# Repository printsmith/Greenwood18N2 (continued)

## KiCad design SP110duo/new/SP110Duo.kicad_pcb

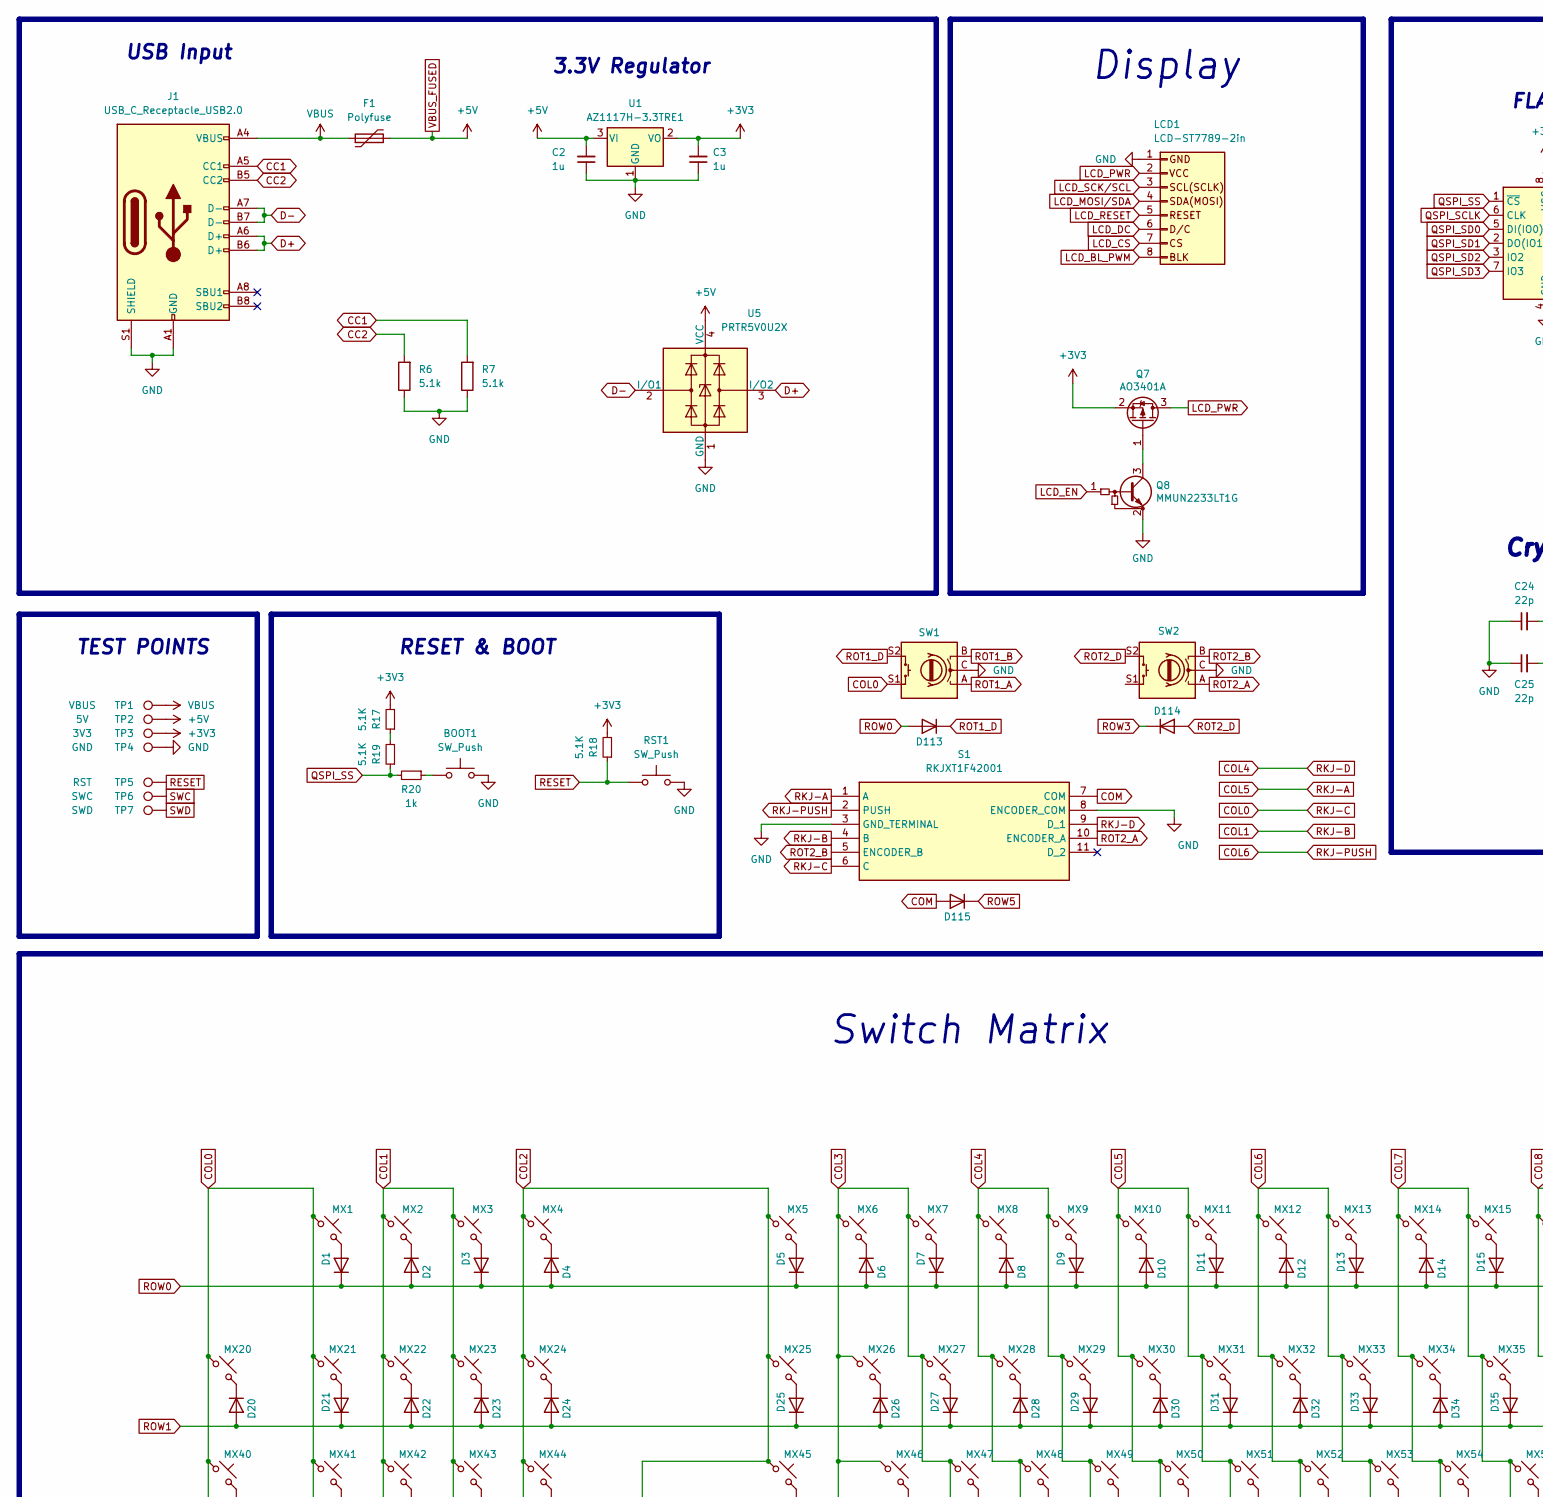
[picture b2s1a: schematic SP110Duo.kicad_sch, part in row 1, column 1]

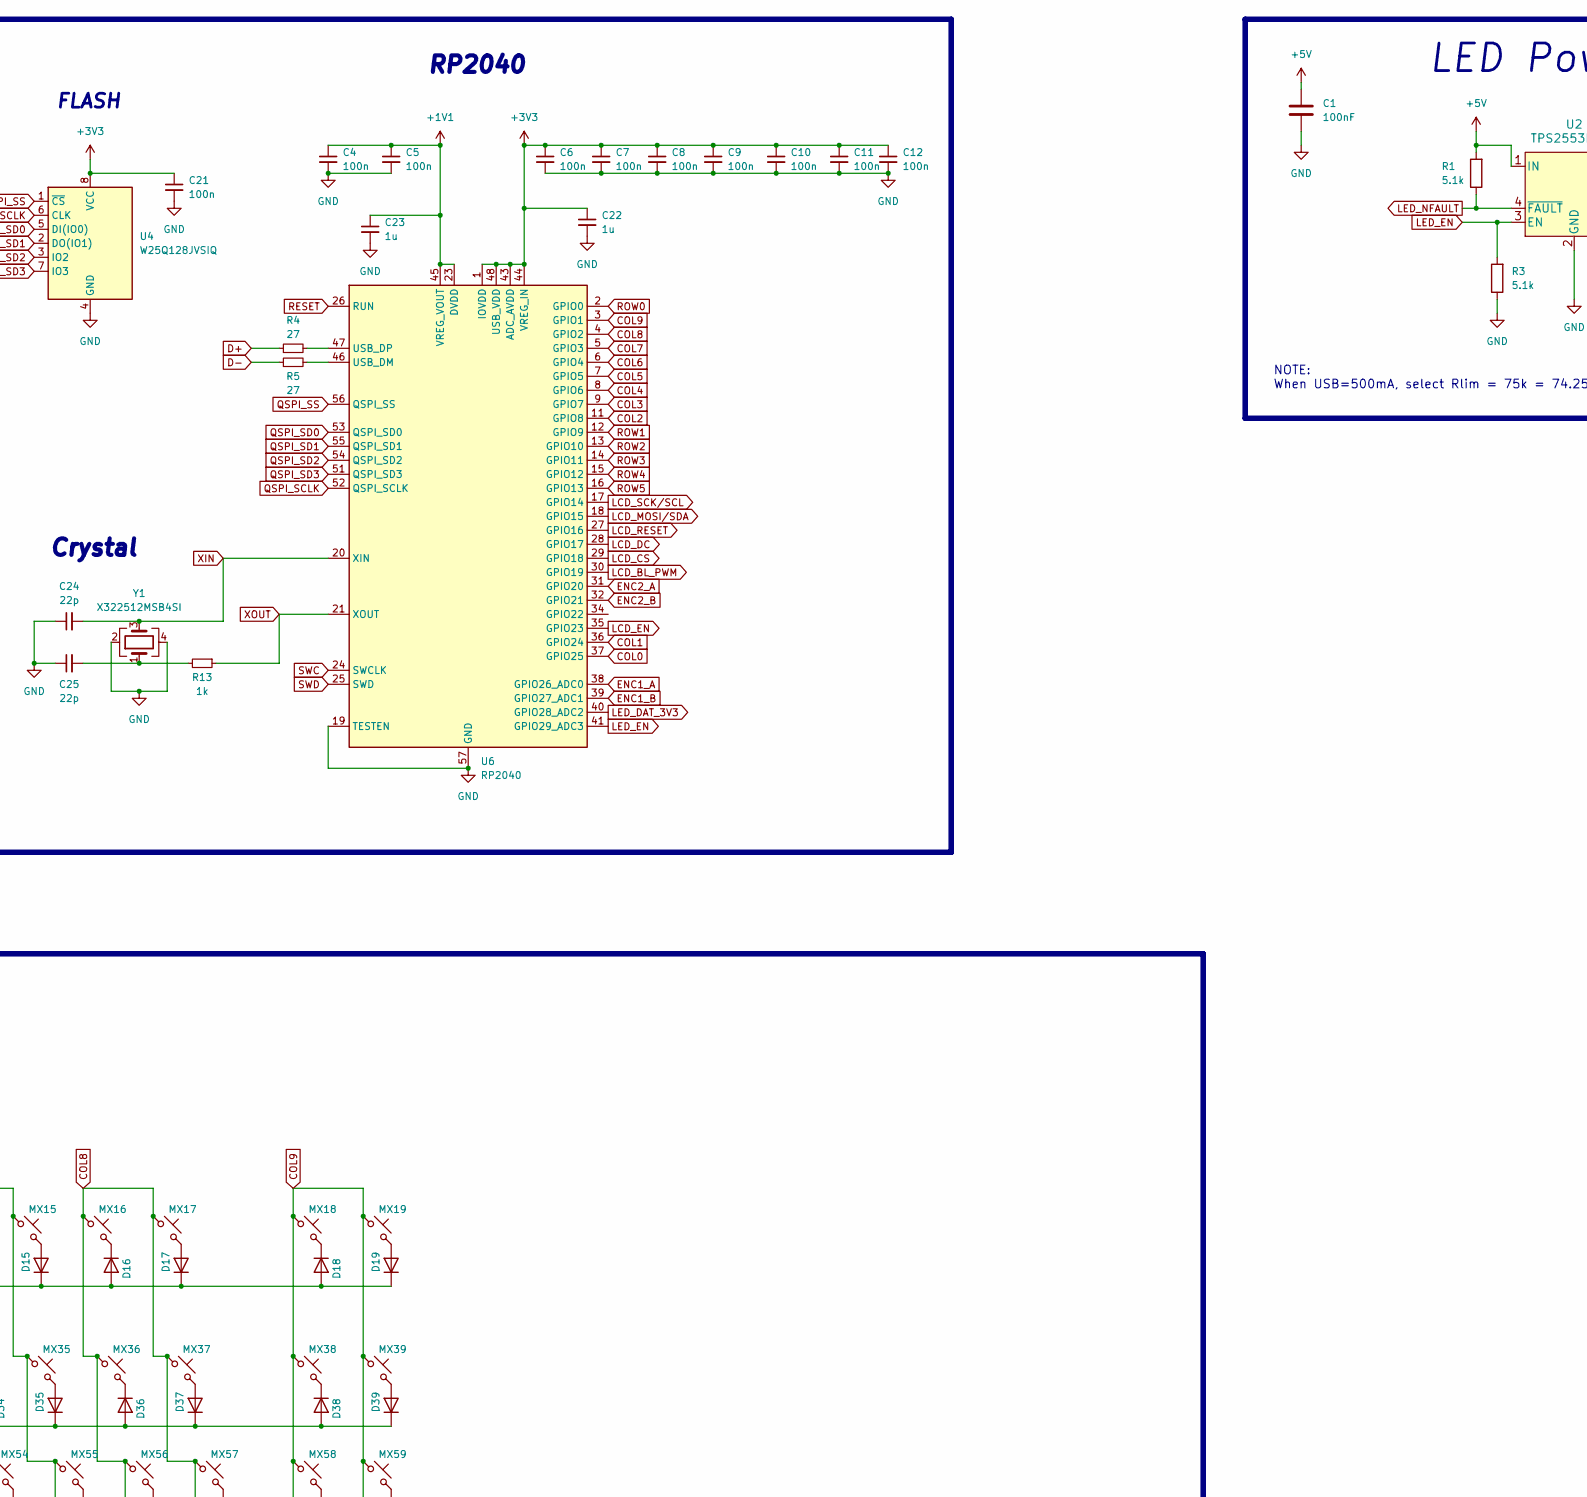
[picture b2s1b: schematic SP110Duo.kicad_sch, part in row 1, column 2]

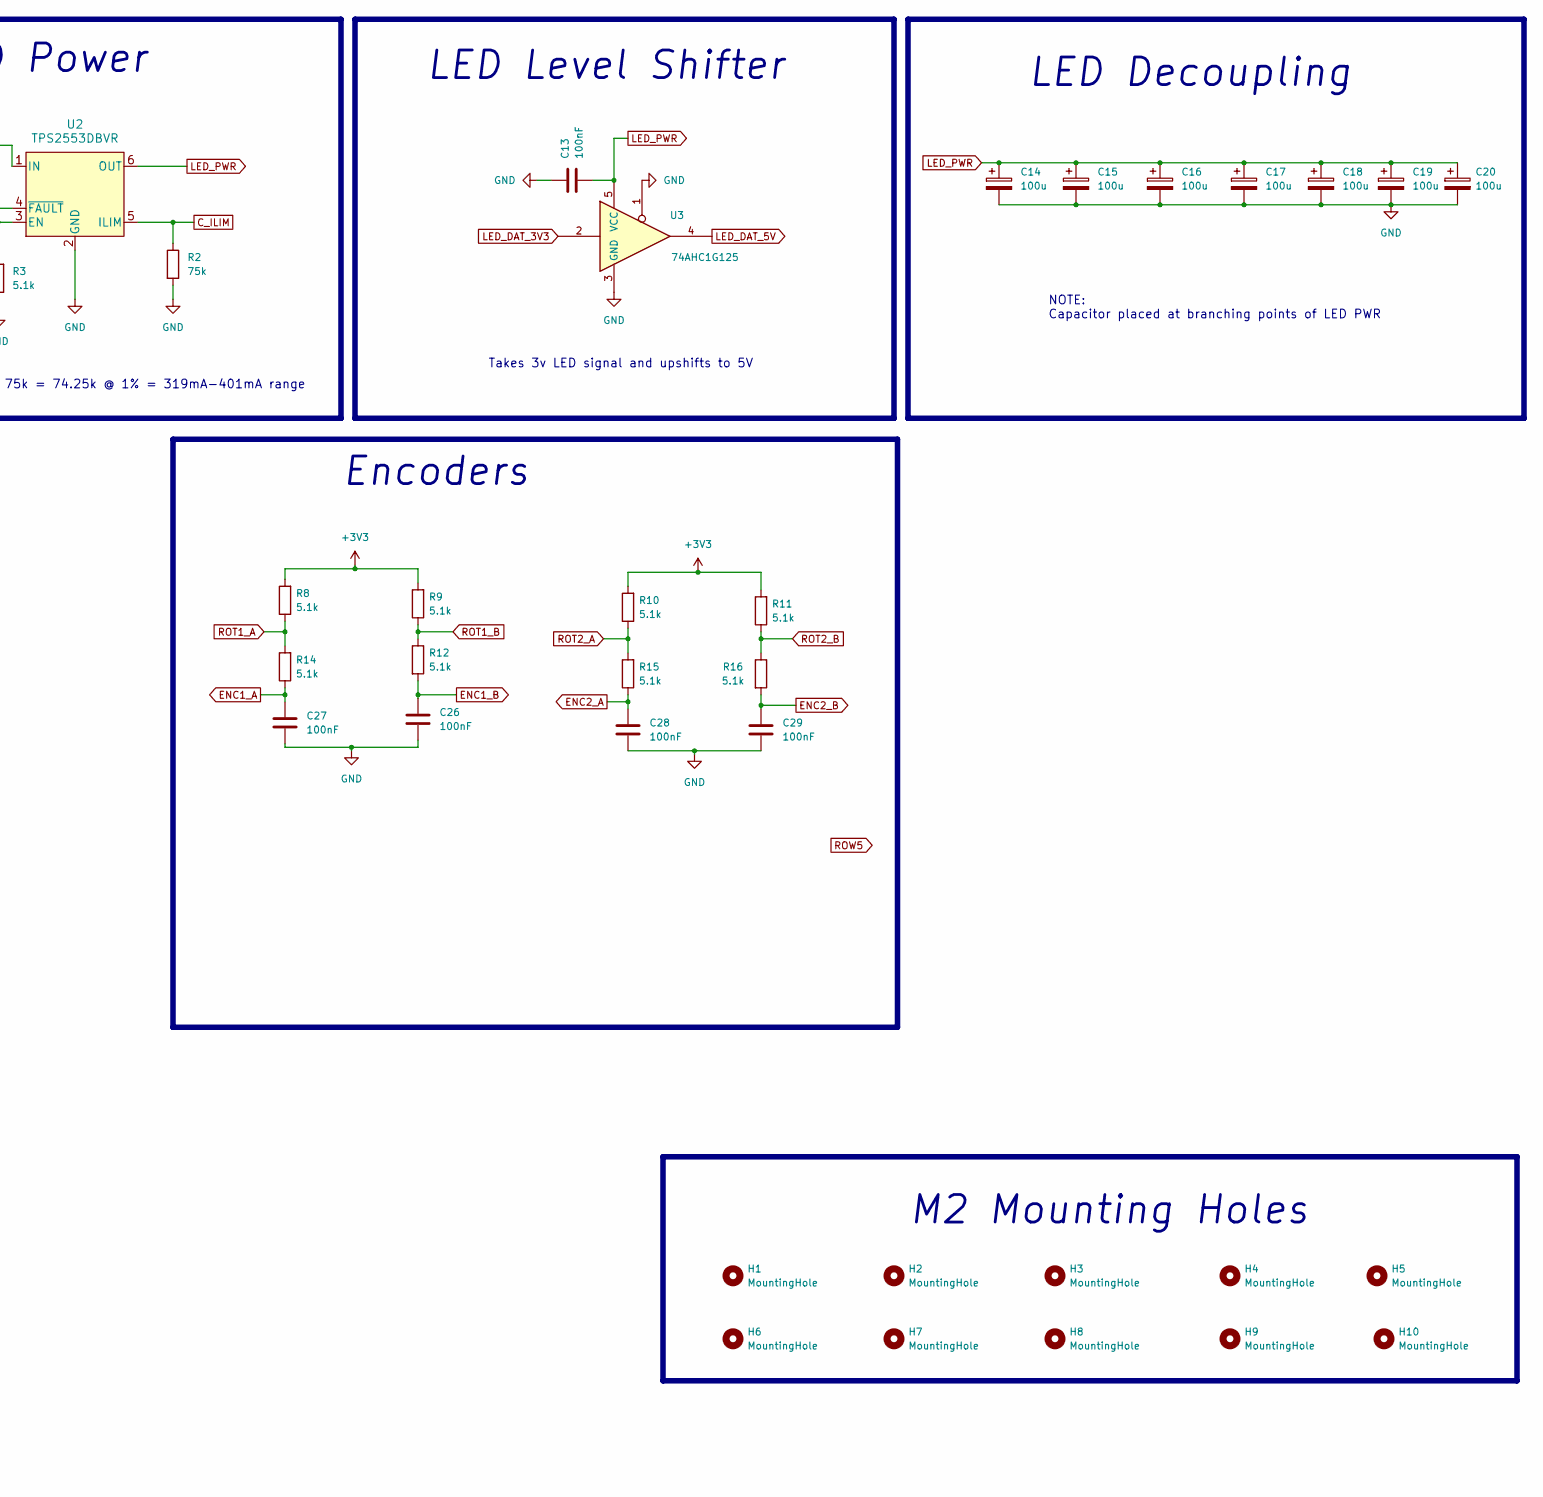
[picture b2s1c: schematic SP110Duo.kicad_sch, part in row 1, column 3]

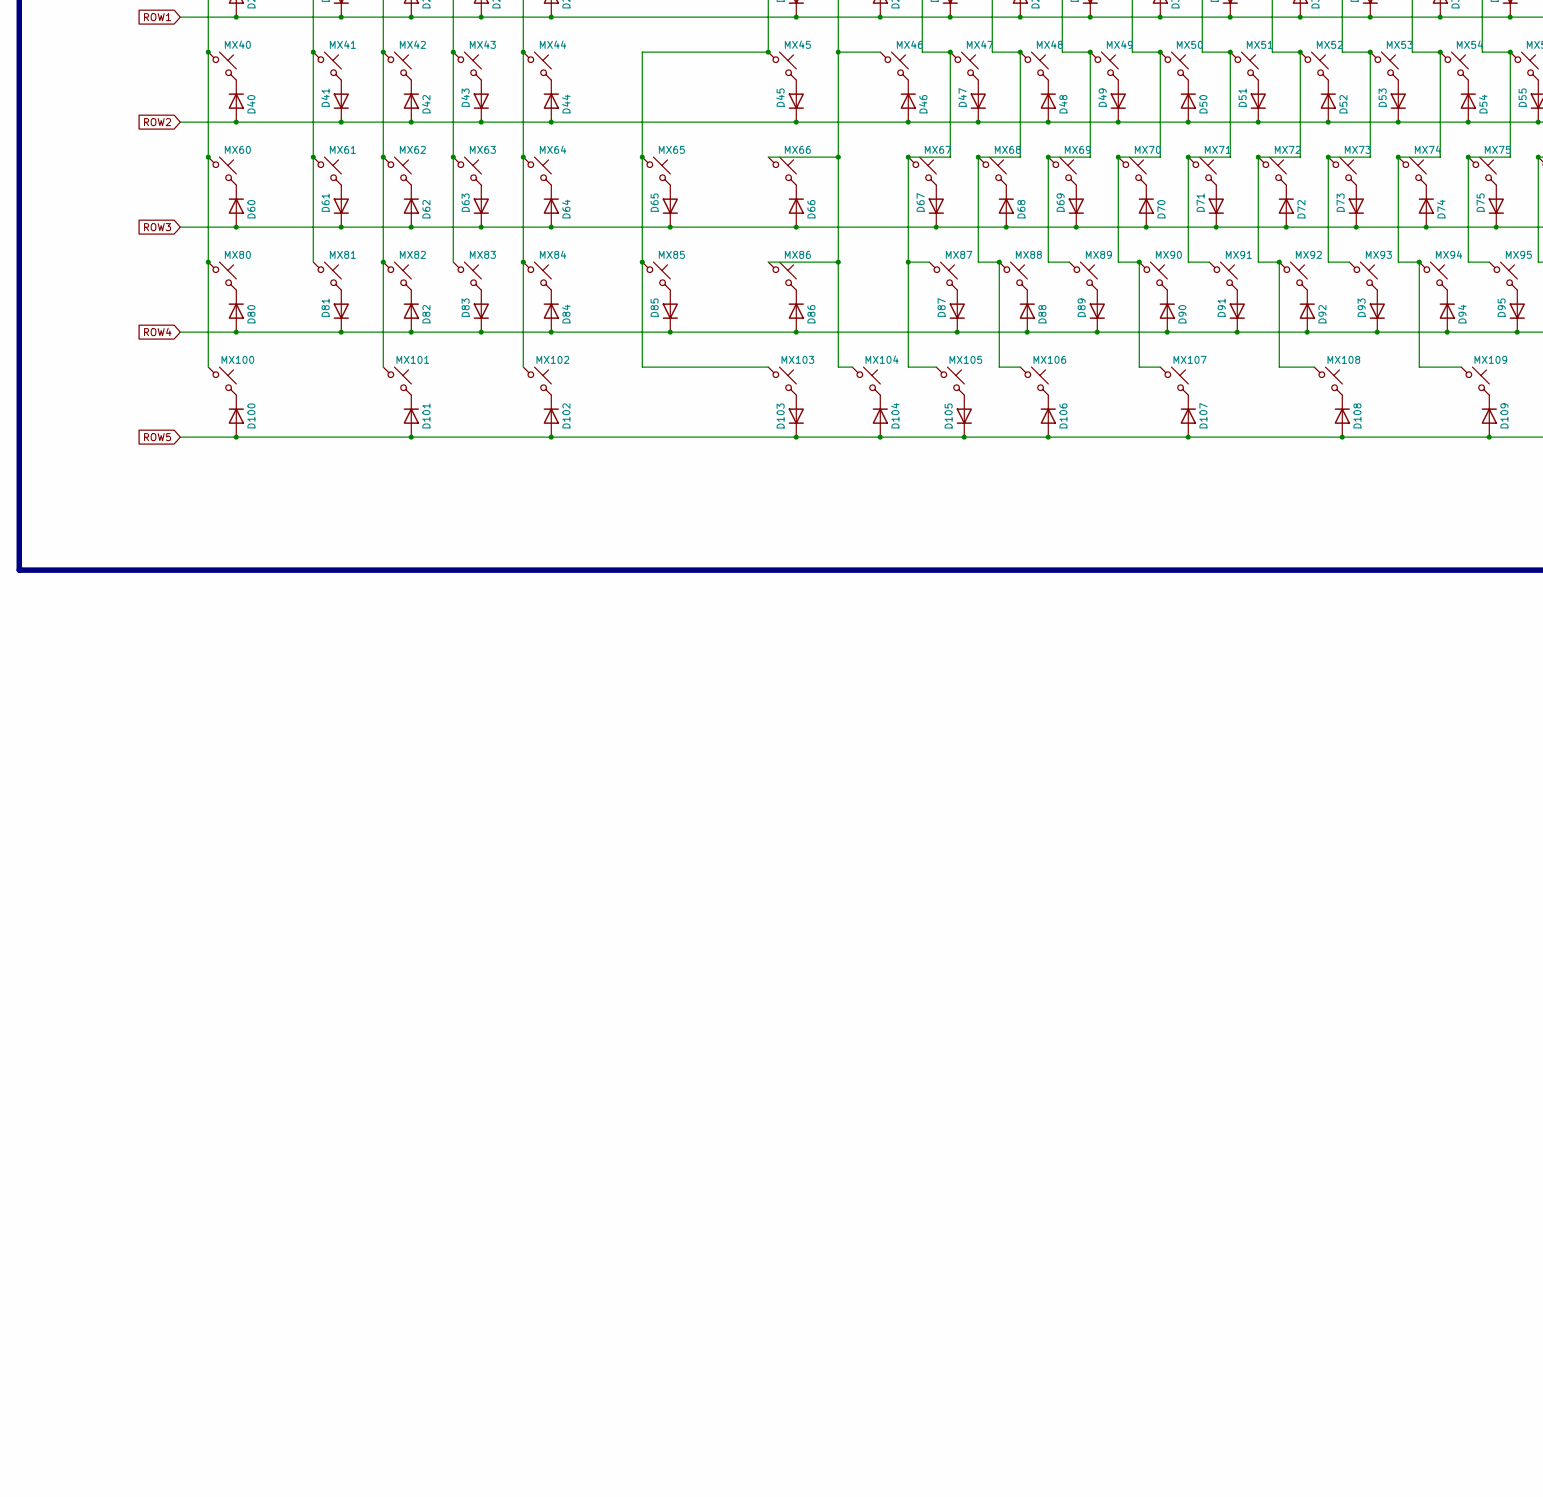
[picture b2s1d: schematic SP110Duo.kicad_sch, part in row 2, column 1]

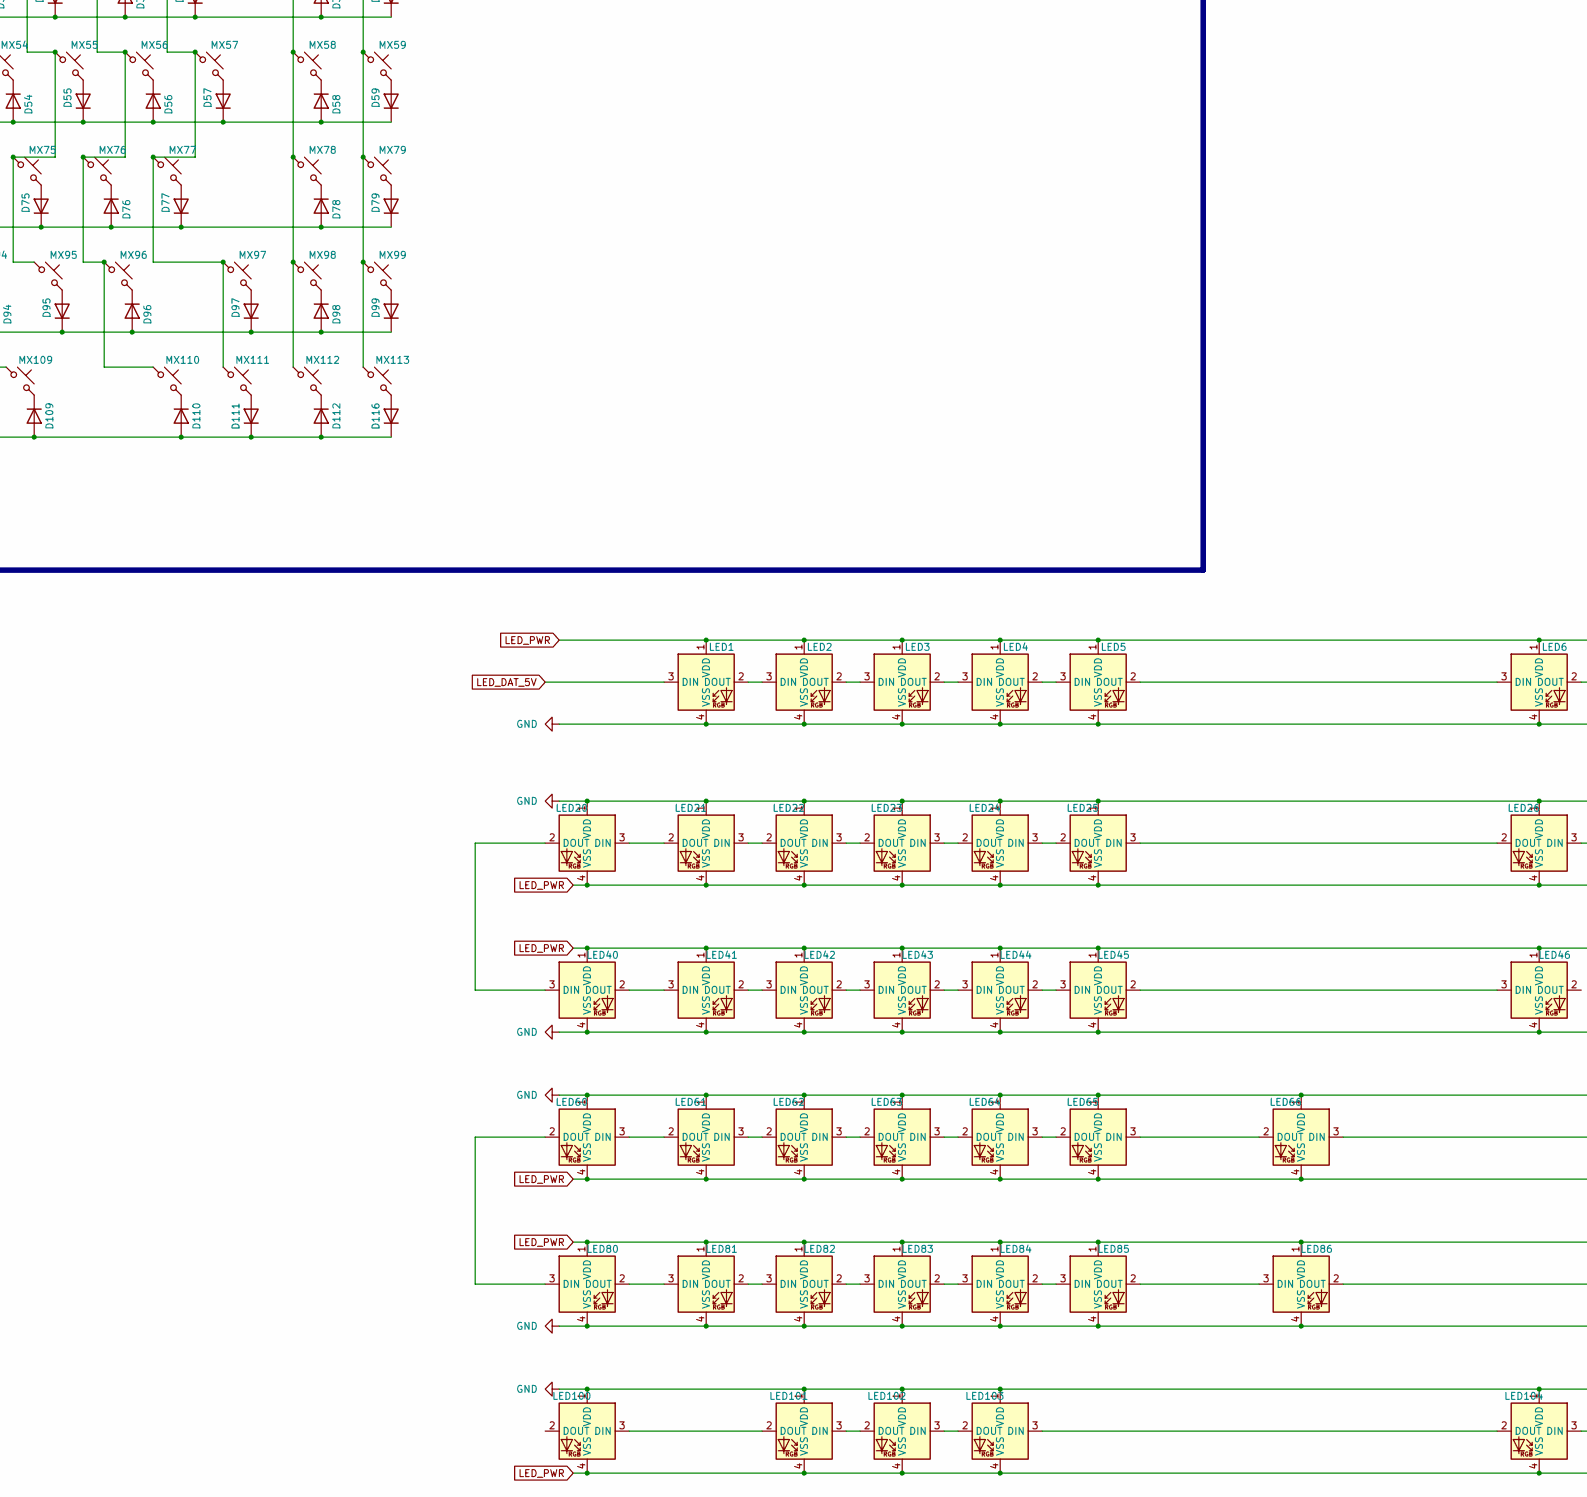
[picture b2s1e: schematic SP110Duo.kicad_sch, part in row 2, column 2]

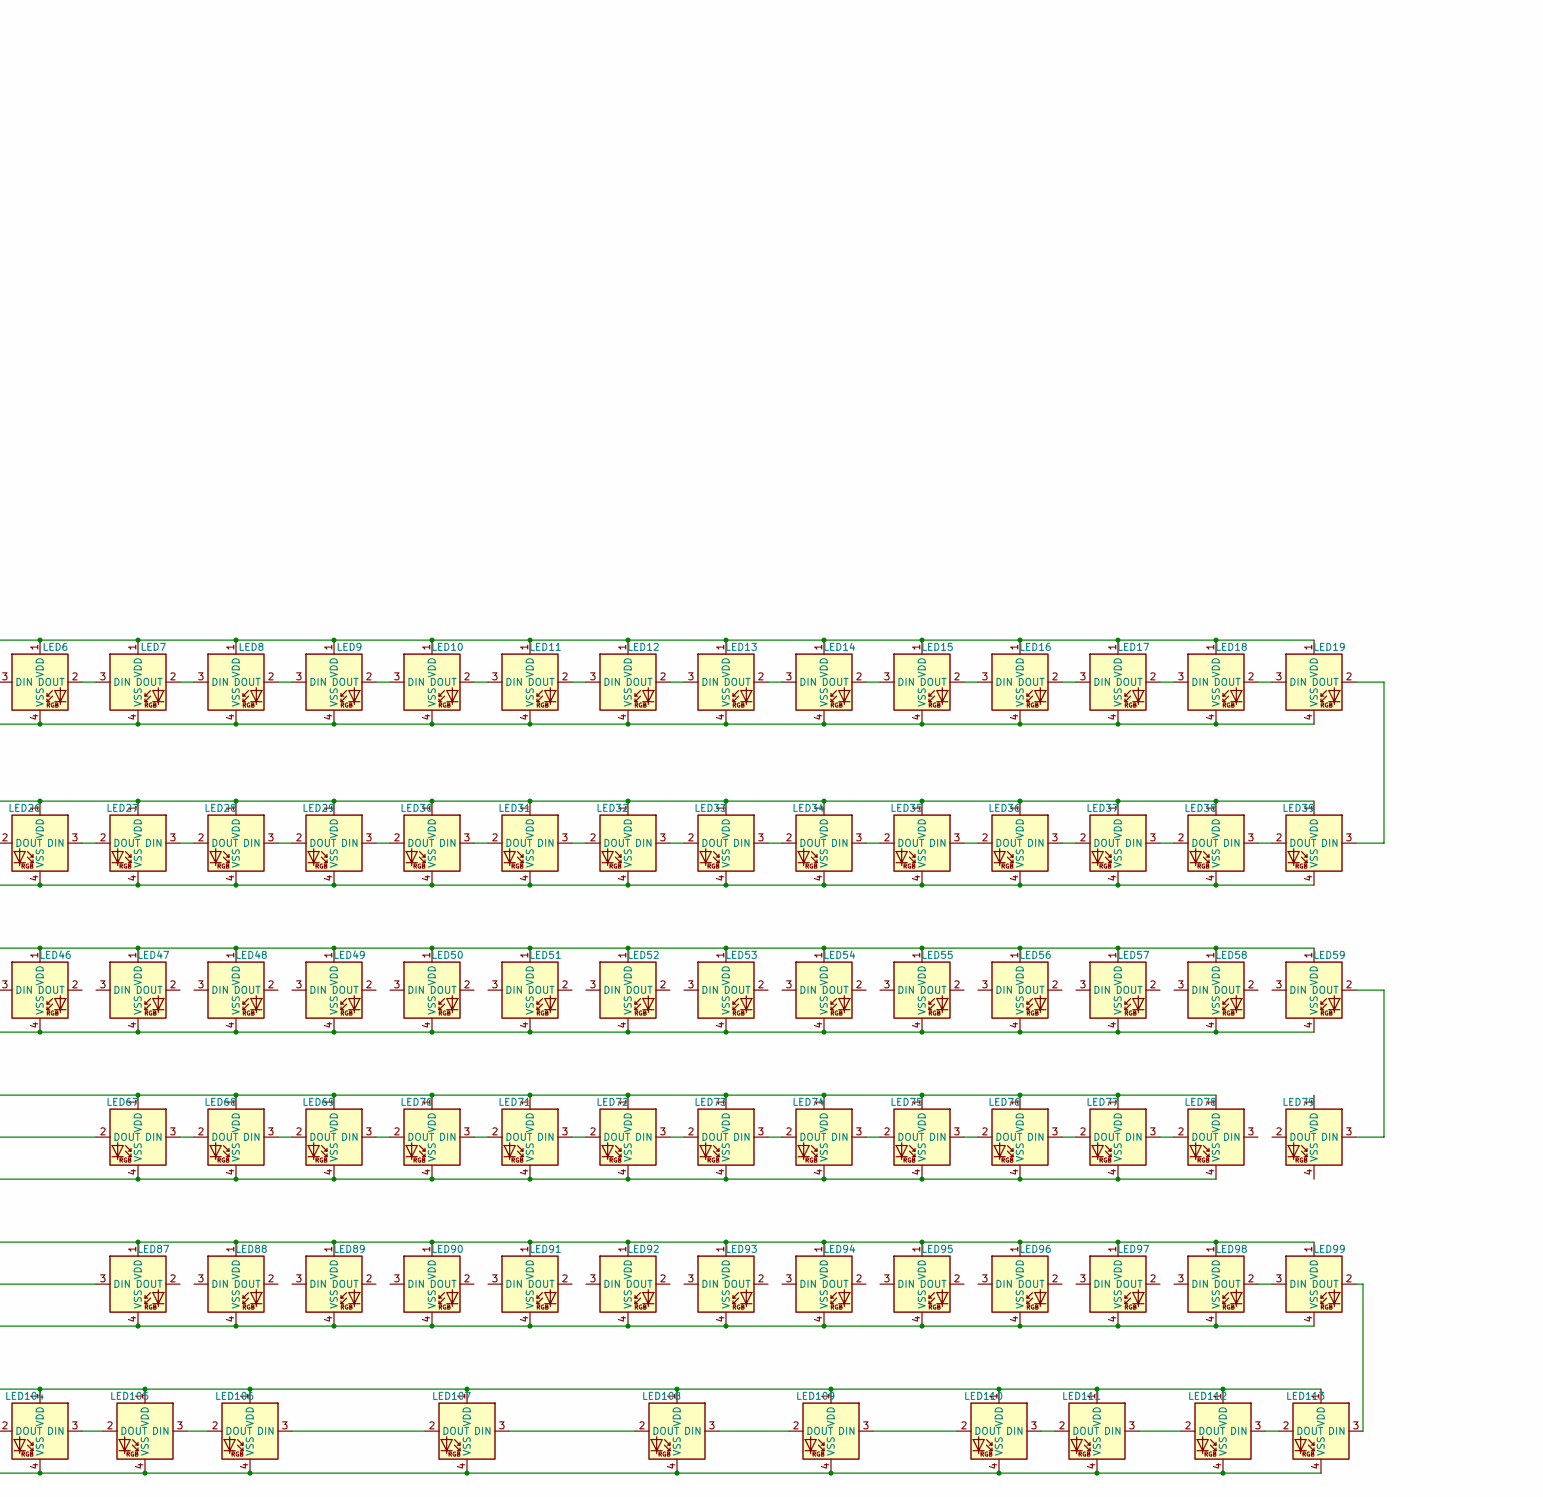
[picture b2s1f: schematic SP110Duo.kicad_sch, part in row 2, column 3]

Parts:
BOOT1: SW_Push; SW_SPST_TL3342
C1, C13: 100nF; C_0402_1005Metric
C2, C3, C22, C23: 1u; C_0402_1005Metric
C4, C5, C6, C7, C8, C9, C10, C11, C12, C21: 100n; C_0402_1005Metric
C14, C15, C16, C17, C18, C19, C20: 100u; CP_EIA-6032-15_Kemet-U
C24, C25: 22p; C_0402_1005Metric
C26, C27, C28, C29: 100nF; C_0805_2012Metric
D1, D2, D3, D4, D5, D6, D7, D8, D9, D10, D11, D12, D13, D14, D15, D16, D17, D18, D19, D20, D21, D22, D23, D24, D25, D26, D27, D28, D29, D30, D31, D32, D33, D34, D35, D36, D37, D38, D39, D40, D41, D42, D43, D44, D45, D46, D47, D48, D49, D50, D51, D52, D53, D54, D55, D56, D57, D58, D59, D60, D61, D62, D63, D64, D65, D66, D67, D68, D69, D70, D71, D72, D73, D74, D75, D76, D77, D78, D79, D80, D81, D82, D83, D84, D85, D86, D87, D88, D89, D90, D91, D92, D93, D94, D95, D96, D97, D98, D99, D100, D101, D102, D103, D104, D105, D106, D107, D108, D109, D110, D111, D112, D113, D114, D115, D116: D; D_SOD-123F
F1: Polyfuse; Fuse_1206_3216Metric_Pad1.42x1.75mm_HandSolder
H1, H2, H3, H4, H5, H6, H7, H8, H9, H10: MountingHole; MountingHole_2.2mm_M2_DIN965_Pad
J1: USB_C_Receptacle_USB2.0; HRO-TYPE-C-31-M-12-modded
LCD1: LCD-ST7789-2in
LED1, LED2, LED3, LED4, LED5, LED6, LED7, LED8, LED9, LED10, LED11, LED12, LED13, LED14, LED15, LED16, LED17, LED18, LED19, LED40, LED41, LED42, LED43, LED44, LED45, LED46, LED47, LED48, LED49, LED50, LED51, LED52, LED53, LED54, LED55, LED56, LED57, LED58, LED59, LED80, LED81, LED82, LED83, LED84, LED85, LED86, LED87, LED88, LED89, LED90, LED91, LED92, LED93, LED94, LED95, LED96, LED97, LED98, LED99: MX_SK6803MINI-E; LED_MX_6028R
LED20, LED21, LED22, LED23, LED24, LED25, LED26, LED27, LED28, LED29, LED30, LED31, LED32, LED33, LED34, LED35, LED36, LED37, LED38, LED39, LED60, LED61, LED62, LED63, LED64, LED65, LED66, LED67, LED68, LED69, LED70, LED71, LED72, LED73, LED74, LED75, LED76, LED77, LED78, LED79, LED100, LED101, LED102, LED103, LED104, LED105, LED106, LED107, LED108, LED109, LED110, LED111, LED112, LED113: MX_SK6803MINI-E; LED_MX_6028R-ROT
MX1, MX2, MX3, MX4, MX5, MX6, MX7, MX8, MX9, MX10, MX11, MX12, MX13, MX14, MX15, MX16, MX17, MX18, MX19, MX20, MX21, MX22, MX23, MX24, MX25, MX26, MX27, MX28, MX29, MX30, MX31, MX32, MX33, MX34, MX35, MX36, MX37, MX38, MX39, MX40, MX41, MX42, MX43, MX44, MX45, MX46, MX47, MX48, MX49, MX50, MX51, MX52, MX53, MX54, MX55, MX56, MX57, MX58, MX59, MX60, MX61, MX62, MX63, MX64, MX65, MX66, MX67, MX68, MX69, MX70, MX71, MX72, MX73, MX74, MX75, MX76, MX77, MX78, MX79, MX80, MX81, MX82, MX83, MX84, MX85, MX86, MX87, MX88, MX89, MX90, MX91, MX92, MX93, MX94, MX95, MX96, MX97, MX98, MX99, MX100, MX101, MX102, MX103, MX104, MX105, MX106, MX107, MX108, MX109, MX110, MX111, MX112, MX113: MX_SW_HS; SW_MX_HS_1u
Q7: AO3401A; SOT-23-3
Q8: MMUN2233LT1G; SOT-23-3
R1, R3, R6, R7: 5.1k; R_0402_1005Metric
R2: 75k; R_0402_1005Metric
R4, R5: 27; R_0402_1005Metric
R8, R9, R10, R11, R12, R14, R15, R16: 5.1k; R_0805_2012Metric
R13, R20: 1k; R_0402_1005Metric
R17, R18, R19: 5.1K; R_0402_1005Metric
RST1: SW_Push; SW_SPST_TL3342
S1: RKJXT1F42001; Mouser Part Number 688-RKJXT1F42001
SW1, SW2: RotaryEncoder_Switch; RotaryEncoder_Alps_EC11E-Switch_Vertical_H20mm_Centred
TP1: VBUS; TestPoint
TP2: 5V; TestPoint
TP3: 3V3; TestPoint
TP4: GND; TestPoint
TP5: RST; TestPoint
TP6: SWC; TestPoint
TP7: SWD; TestPoint
U1: AZ1117H-3.3TRE1; SOT-223-3_TabPin2
U2: TPS2553DBVR; SOT-23-6
U3: 74AHC1G125; SOT-23-5
U4: W25Q128JVSIQ; SOIC-8_5.275x5.275mm_P1.27mm
U5: PRTR5V0U2X; SOT-143_Handsoldering
U6: RP2040; QFN-56-1EP_7x7mm_P0.4mm_EP3.2x3.2mm
Y1: X322512MSB4SI; Crystal_SMD_3225-4Pin_3.2x2.5mm

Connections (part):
+1V1: C4.1, C5.1, C23.1, U6.23 (DVDD), U6.45 (VREG_VOUT), U6.50 (DVDD)
+3V3: C3.2, C6.1, C7.1, C8.1, C9.1, C10.1, C11.1, C12.1, C21.1, C22.1, R8.2, R9.2, R10.2, R11.2, R17.2, R18.2, TP3.1, U1.2 (VO), U4.8 (VCC), U6.1 (IOVDD), U6.10 (IOVDD), U6.22 (IOVDD), U6.33 (IOVDD), U6.42 (IOVDD), U6.43 (ADC_AVDD), U6.44 (VREG_IN), U6.48 (USB_VDD), U6.49 (IOVDD); also elsewhere on the board
CC1: J1.A5 (CC1), R7.2
CC2: J1.B5 (CC2), R6.2
COL0: MX1.1, MX20.1, MX21.1, MX40.1, MX41.1, MX60.1, MX61.1, MX80.1, MX81.1, MX100.1, S1.6 (C), SW1.S1, U6.37 (GPIO25)
COL1: MX2.1, MX3.1, MX22.1, MX23.1, MX42.1, MX43.1, MX62.1, MX63.1, MX82.1, MX83.1, MX101.1, S1.4 (B), U6.36 (GPIO24)
COL2: MX4.1, MX5.1, MX24.1, MX25.1, MX44.1, MX45.1, MX64.1, MX65.1, MX84.1, MX85.1, MX102.1, MX103.1, U6.11 (GPIO8)
COL3: MX6.1, MX7.1, MX26.1, MX27.1, MX46.1, MX47.1, MX66.1, MX67.1, MX86.1, MX87.1, MX104.1, MX105.1, U6.9 (GPIO7)
COL4: MX8.1, MX9.1, MX28.1, MX29.1, MX48.1, MX49.1, MX68.1, MX69.1, MX88.1, MX89.1, MX106.1, S1.9 (D_1), U6.8 (GPIO6)
COL5: MX10.1, MX11.1, MX30.1, MX31.1, MX50.1, MX51.1, MX70.1, MX71.1, MX90.1, MX91.1, MX107.1, S1.1 (A), U6.7 (GPIO5)
COL6: MX12.1, MX13.1, MX32.1, MX33.1, MX52.1, MX53.1, MX72.1, MX73.1, MX92.1, MX93.1, MX108.1, S1.2 (PUSH), U6.6 (GPIO4)
COL7: MX14.1, MX15.1, MX34.1, MX35.1, MX54.1, MX55.1, MX74.1, MX75.1, MX94.1, MX95.1, MX109.1, U6.5 (GPIO3)
COL8: MX16.1, MX17.1, MX36.1, MX37.1, MX56.1, MX57.1, MX76.1, MX77.1, MX96.1, MX97.1, MX110.1, MX111.1, U6.4 (GPIO2)
COL9: MX18.1, MX19.1, MX38.1, MX39.1, MX58.1, MX59.1, MX78.1, MX79.1, MX98.1, MX99.1, MX112.1, MX113.1, U6.3 (GPIO1)
COM: D115.2 (A), S1.7 (COM)
C_ILIM: R2.1, U2.5 (ILIM)
D+: J1.A6 (D+), J1.B6 (D+), R4.1, U5.3 (I/O2)
D-: J1.A7 (D-), J1.B7 (D-), R5.1, U5.2 (I/O1)
ENC1_A: C27.2, R14.1, U6.38 (GPIO26_ADC0)
ENC1_B: C26.2, R12.2, U6.39 (GPIO27_ADC1)
ENC2_A: C28.2, R15.1, U6.31 (GPIO20)
ENC2_B: C29.2, R16.2, U6.32 (GPIO21)
GND: BOOT1.2, C1.1, C2.1, C3.1, C4.2, C5.2, C6.2, C7.2, C8.2, C9.2, C10.2, C11.2, C12.2, C13.2, C14.2, C15.2, C16.2, C17.2, C18.2, C19.2, C20.2, C21.2, C22.2, C23.2, C24.1, C25.1, C26.1, C27.1, C28.1, C29.1, J1.A1 (GND), J1.A12 (GND), J1.B1 (GND), J1.B12 (GND), J1.S1 (SHIELD), LCD1.1, LED1.4 (VSS), LED2.4 (VSS), LED3.4 (VSS), LED4.4 (VSS), LED5.4 (VSS), LED6.4 (VSS), LED7.4 (VSS), LED8.4 (VSS), LED9.4 (VSS), LED10.4 (VSS), LED11.4 (VSS), LED12.4 (VSS), LED13.4 (VSS), LED14.4 (VSS), LED15.4 (VSS), LED16.4 (VSS), LED17.4 (VSS), LED18.4 (VSS), LED19.4 (VSS), LED20.1 (VDD), LED21.1 (VDD), LED22.1 (VDD), LED23.1 (VDD), LED24.1 (VDD), LED25.1 (VDD), LED26.1 (VDD), LED27.1 (VDD), LED28.1 (VDD), LED29.1 (VDD), LED30.1 (VDD), LED31.1 (VDD), LED32.1 (VDD), LED33.1 (VDD), LED34.1 (VDD), LED35.1 (VDD), LED36.1 (VDD), LED37.1 (VDD), LED38.1 (VDD), LED39.1 (VDD), LED40.4 (VSS), LED41.4 (VSS), LED42.4 (VSS), LED43.4 (VSS), LED44.4 (VSS)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; also elsewhere on the board
LCD_BL_PWM: LCD1.8, U6.30 (GPIO19)
LCD_CS: LCD1.7, U6.29 (GPIO18)
LCD_DC: LCD1.6, U6.28 (GPIO17)
LCD_EN: U6.35 (GPIO23); also elsewhere on the board
LCD_MOSI/SDA: LCD1.4, U6.18 (GPIO15)
LCD_PWR: LCD1.2; also elsewhere on the board
LCD_RESET: LCD1.5, U6.27 (GPIO16)
LCD_SCK/SCL: LCD1.3, U6.17 (GPIO14)
LED_DAT_3V3: U3.2, U6.40 (GPIO28_ADC2)
LED_DAT_5V: LED1.3 (DIN), U3.4
LED_EN: R3.2, U2.3 (EN), U6.41 (GPIO29_ADC3)
LED_NFAULT: R1.1, U2.4 (~FAULT)
LED_PWR: C13.1, C14.1, C15.1, C16.1, C17.1, C18.1, C19.1, C20.1, LED1.1 (VDD), LED2.1 (VDD), LED3.1 (VDD), LED4.1 (VDD), LED5.1 (VDD), LED6.1 (VDD), LED7.1 (VDD), LED8.1 (VDD), LED9.1 (VDD), LED10.1 (VDD), LED11.1 (VDD), LED12.1 (VDD), LED13.1 (VDD), LED14.1 (VDD), LED15.1 (VDD), LED16.1 (VDD), LED17.1 (VDD), LED18.1 (VDD), LED19.1 (VDD), LED20.4 (VSS), LED21.4 (VSS), LED22.4 (VSS), LED23.4 (VSS), LED24.4 (VSS), LED25.4 (VSS), LED26.4 (VSS), LED27.4 (VSS), LED28.4 (VSS), LED29.4 (VSS), LED30.4 (VSS), LED31.4 (VSS), LED32.4 (VSS), LED33.4 (VSS), LED34.4 (VSS), LED35.4 (VSS), LED36.4 (VSS), LED37.4 (VSS), LED38.4 (VSS), LED39.4 (VSS), LED40.1 (VDD), LED41.1 (VDD), LED42.1 (VDD), LED43.1 (VDD), LED44.1 (VDD), LED45.1 (VDD), LED46.1 (VDD), LED47.1 (VDD), LED48.1 (VDD), LED49.1 (VDD), LED50.1 (VDD), LED51.1 (VDD), LED52.1 (VDD), LED53.1 (VDD), LED54.1 (VDD), LED55.1 (VDD), LED56.1 (VDD), LED57.1 (VDD), LED58.1 (VDD), LED59.1 (VDD), LED60.4 (VSS), LED61.4 (VSS), LED62.4 (VSS), LED63.4 (VSS), LED64.4 (VSS), LED65.4 (VSS), LED66.4 (VSS), LED67.4 (VSS), LED68.4 (VSS), LED69.4 (VSS), LED70.4 (VSS), LED71.4 (VSS), LED72.4 (VSS)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
unnamed: BOOT1.1, R20.1
unnamed: C25.2, R13.2, Y1.1
unnamed: D1.2 (A), MX1.2
unnamed: D2.1 (K), MX2.2
unnamed: D3.2 (A), MX3.2
unnamed: D4.1 (K), MX4.2
unnamed: D5.2 (A), MX5.2
unnamed: D6.1 (K), MX6.2
unnamed: D7.2 (A), MX7.2
unnamed: D8.1 (K), MX8.2
unnamed: D9.2 (A), MX9.2
unnamed: D10.1 (K), MX10.2
unnamed: D11.2 (A), MX11.2
unnamed: D12.1 (K), MX12.2
unnamed: D13.2 (A), MX13.2
unnamed: D14.1 (K), MX14.2
unnamed: D15.2 (A), MX15.2
unnamed: D16.1 (K), MX16.2
unnamed: D17.2 (A), MX17.2
unnamed: D18.1 (K), MX18.2
unnamed: D19.2 (A), MX19.2
unnamed: D20.1 (K), MX20.2
unnamed: D21.2 (A), MX21.2
unnamed: D22.1 (K), MX22.2
unnamed: D23.1 (K), MX23.2
unnamed: D24.1 (K), MX24.2
unnamed: D25.2 (A), MX25.2
unnamed: D26.1 (K), MX26.2
unnamed: D27.2 (A), MX27.2
unnamed: D28.1 (K), MX28.2
unnamed: D29.2 (A), MX29.2
unnamed: D30.1 (K), MX30.2
unnamed: D31.2 (A), MX31.2
unnamed: D32.1 (K), MX32.2
unnamed: D33.2 (A), MX33.2
unnamed: D34.1 (K), MX34.2
unnamed: D35.2 (A), MX35.2
unnamed: D36.1 (K), MX36.2
unnamed: D37.2 (A), MX37.2
unnamed: D38.1 (K), MX38.2
unnamed: D39.2 (A), MX39.2
unnamed: D40.1 (K), MX40.2
unnamed: D41.2 (A), MX41.2
unnamed: D42.1 (K), MX42.2
unnamed: D43.2 (A), MX43.2
unnamed: D44.1 (K), MX44.2
unnamed: D45.2 (A), MX45.2
unnamed: D46.1 (K), MX46.2
unnamed: D47.2 (A), MX47.2
unnamed: D48.1 (K), MX48.2
unnamed: D49.2 (A), MX49.2
unnamed: D50.1 (K), MX50.2
unnamed: D51.2 (A), MX51.2
unnamed: D52.1 (K), MX52.2
unnamed: D53.2 (A), MX53.2
unnamed: D54.1 (K), MX54.2
unnamed: D55.2 (A), MX55.2
unnamed: D56.1 (K), MX56.2
unnamed: D57.2 (A), MX57.2
unnamed: D58.1 (K), MX58.2
unnamed: D59.2 (A), MX59.2
unnamed: D60.1 (K), MX60.2
unnamed: D61.2 (A), MX61.2
unnamed: D62.1 (K), MX62.2
unnamed: D63.2 (A), MX63.2
unnamed: D64.1 (K), MX64.2
unnamed: D65.2 (A), MX65.2
unnamed: D66.1 (K), MX66.2
unnamed: D67.2 (A), MX67.2
unnamed: D68.1 (K), MX68.2
unnamed: D69.2 (A), MX69.2
unnamed: D70.1 (K), MX70.2
unnamed: D71.2 (A), MX71.2
unnamed: D72.1 (K), MX72.2
unnamed: D73.2 (A), MX73.2
unnamed: D74.1 (K), MX74.2
unnamed: D75.2 (A), MX75.2
unnamed: D76.1 (K), MX76.2
unnamed: D77.2 (A), MX77.2
unnamed: D78.1 (K), MX78.2
unnamed: D79.2 (A), MX79.2
unnamed: D80.1 (K), MX80.2
unnamed: D81.2 (A), MX81.2
unnamed: D82.1 (K), MX82.2
unnamed: D83.2 (A), MX83.2
unnamed: D84.1 (K), MX84.2
unnamed: D85.2 (A), MX85.2
unnamed: D86.1 (K), MX86.2
unnamed: D87.2 (A), MX87.2
unnamed: D88.1 (K), MX88.2
unnamed: D89.2 (A), MX89.2
unnamed: D90.1 (K), MX90.2
unnamed: D91.2 (A), MX91.2
unnamed: D92.1 (K), MX92.2
unnamed: D93.2 (A), MX93.2
unnamed: D94.1 (K), MX94.2
unnamed: D95.2 (A), MX95.2
unnamed: D96.1 (K), MX96.2
unnamed: D97.2 (A), MX97.2
unnamed: D98.1 (K), MX98.2
unnamed: D99.2 (A), MX99.2
unnamed: D100.1 (K), MX100.2
unnamed: D101.1 (K), MX101.2
unnamed: D102.1 (K), MX102.2
unnamed: D103.2 (A), MX103.2
unnamed: D104.1 (K), MX104.2
unnamed: D105.2 (A), MX105.2
unnamed: D106.1 (K), MX106.2
unnamed: D107.1 (K), MX107.2
unnamed: D108.1 (K), MX108.2
unnamed: D109.1 (K), MX109.2
unnamed: D110.1 (K), MX110.2
unnamed: D111.2 (A), MX111.2
unnamed: D112.1 (K), MX112.2
unnamed: D116.2 (A), MX113.2
unnamed: LED1.2 (DOUT), LED2.3 (DIN)
unnamed: LED2.2 (DOUT), LED3.3 (DIN)
unnamed: LED3.2 (DOUT), LED4.3 (DIN)
unnamed: LED4.2 (DOUT), LED5.3 (DIN)
unnamed: LED5.2 (DOUT), LED6.3 (DIN)
unnamed: LED6.2 (DOUT), LED7.3 (DIN)
unnamed: LED7.2 (DOUT), LED8.3 (DIN)
unnamed: LED8.2 (DOUT), LED9.3 (DIN)
unnamed: LED9.2 (DOUT), LED10.3 (DIN)
unnamed: LED10.2 (DOUT), LED11.3 (DIN)
unnamed: LED11.2 (DOUT), LED12.3 (DIN)
unnamed: LED12.2 (DOUT), LED13.3 (DIN)
unnamed: LED13.2 (DOUT), LED14.3 (DIN)
unnamed: LED14.2 (DOUT), LED15.3 (DIN)
unnamed: LED15.2 (DOUT), LED16.3 (DIN)
unnamed: LED16.2 (DOUT), LED17.3 (DIN)
unnamed: LED17.2 (DOUT), LED18.3 (DIN)
unnamed: LED18.2 (DOUT), LED19.3 (DIN)
unnamed: LED19.2 (DOUT), LED39.3 (DIN)
unnamed: LED20.3 (DIN), LED21.2 (DOUT)
unnamed: LED20.2 (DOUT), LED40.3 (DIN)
unnamed: LED21.3 (DIN), LED22.2 (DOUT)
unnamed: LED22.3 (DIN), LED23.2 (DOUT)
unnamed: LED23.3 (DIN), LED24.2 (DOUT)
unnamed: LED24.3 (DIN), LED25.2 (DOUT)
unnamed: LED25.3 (DIN), LED26.2 (DOUT)
unnamed: LED26.3 (DIN), LED27.2 (DOUT)
unnamed: LED27.3 (DIN), LED28.2 (DOUT)
unnamed: LED28.3 (DIN), LED29.2 (DOUT)
unnamed: LED29.3 (DIN), LED30.2 (DOUT)
unnamed: LED30.3 (DIN), LED31.2 (DOUT)
unnamed: LED31.3 (DIN), LED32.2 (DOUT)
unnamed: LED32.3 (DIN), LED33.2 (DOUT)
unnamed: LED33.3 (DIN), LED34.2 (DOUT)
unnamed: LED34.3 (DIN), LED35.2 (DOUT)
unnamed: LED35.3 (DIN), LED36.2 (DOUT)
unnamed: LED36.3 (DIN), LED37.2 (DOUT)
unnamed: LED37.3 (DIN), LED38.2 (DOUT)
unnamed: LED38.3 (DIN), LED39.2 (DOUT)
unnamed: LED40.2 (DOUT), LED41.3 (DIN)
unnamed: LED41.2 (DOUT), LED42.3 (DIN)
unnamed: LED42.2 (DOUT), LED43.3 (DIN)
unnamed: LED43.2 (DOUT), LED44.3 (DIN)
unnamed: LED44.2 (DOUT), LED45.3 (DIN)
unnamed: LED45.2 (DOUT), LED46.3 (DIN)
unnamed: LED59.2 (DOUT), LED79.3 (DIN)
unnamed: LED60.3 (DIN), LED61.2 (DOUT)
unnamed: LED60.2 (DOUT), LED80.3 (DIN)
unnamed: LED61.3 (DIN), LED62.2 (DOUT)
unnamed: LED62.3 (DIN), LED63.2 (DOUT)
unnamed: LED63.3 (DIN), LED64.2 (DOUT)
unnamed: LED64.3 (DIN), LED65.2 (DOUT)
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
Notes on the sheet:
TEST POINTS
Encoders
LED Decoupling
Takes 3v LED signal and upshifts to 5V
Crystal
FLASH
USB Input
LED Level Shifter
Display
NOTE: When USB=500mA, select Rlim = 75k = 74.25k @ 1% = 319mA-401mA range
M2 Mounting Holes
NOTE: Capacitor placed at branching points of LED PWR
RP2040
Switch Matrix
LED Power
RESET & BOOT
3.3V Regulator

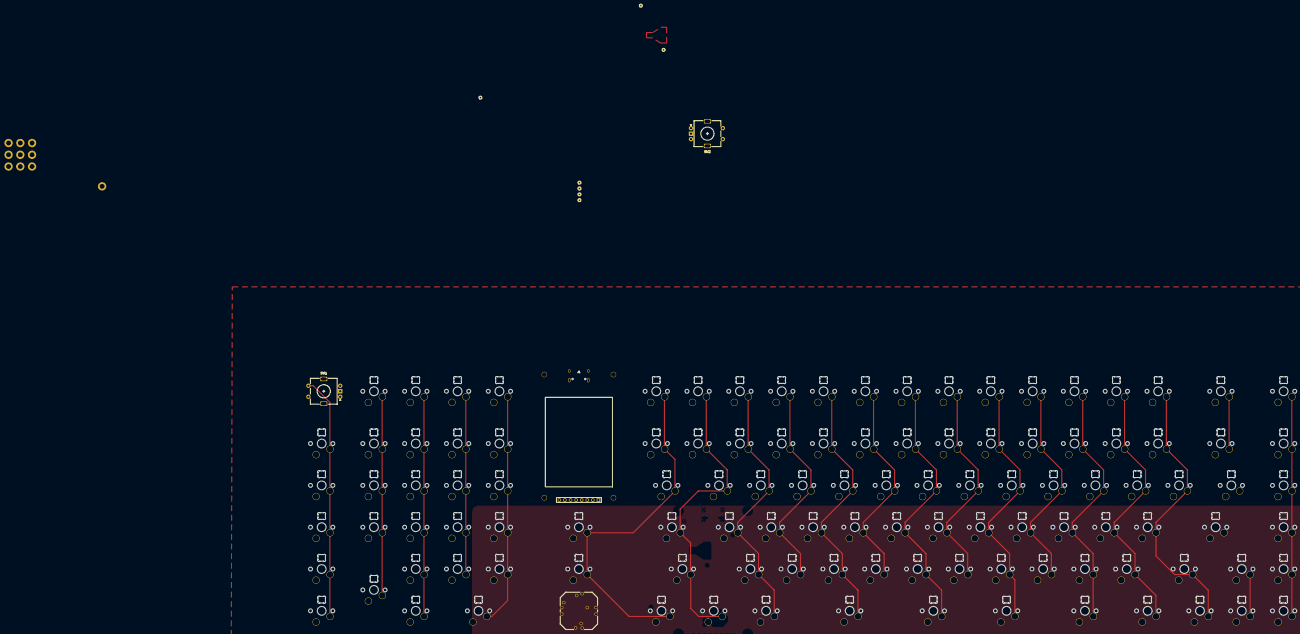
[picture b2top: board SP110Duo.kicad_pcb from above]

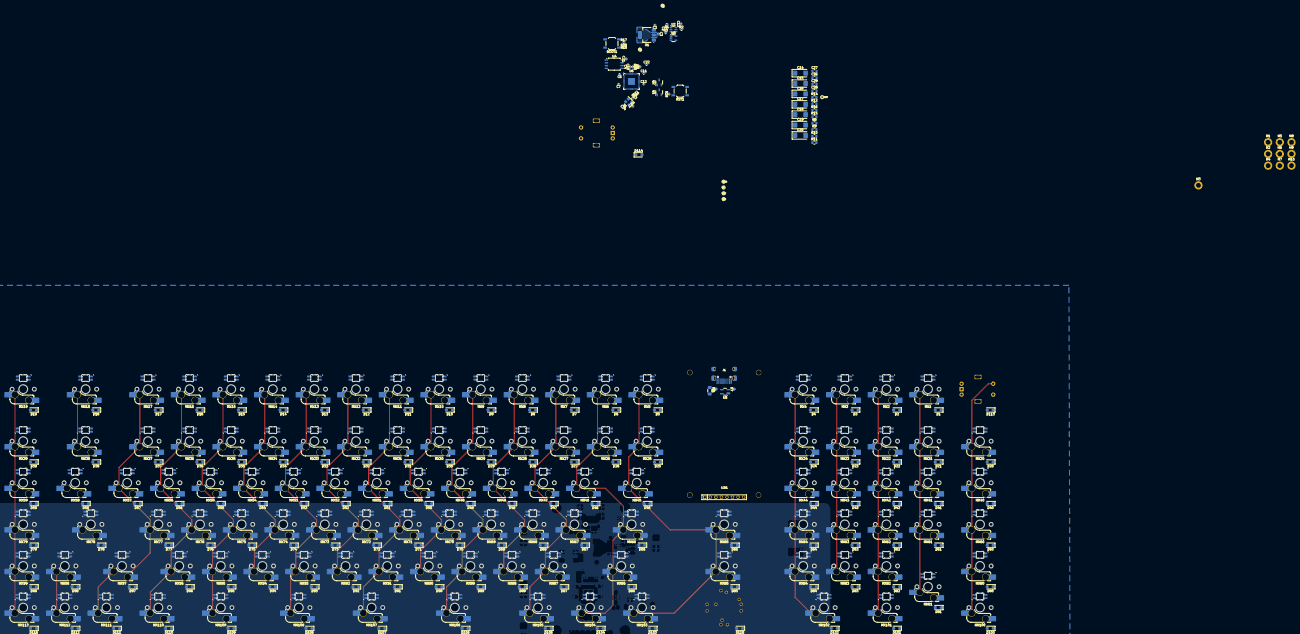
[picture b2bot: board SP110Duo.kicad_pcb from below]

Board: 2 copper layers, 425 parts (417 on the bottom side), 267 nets.

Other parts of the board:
Q1: AO3401A; SOT-23-3
Q2: MMUN2233LT1G; SOT-23-3

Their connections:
+3V3: Q1.2 (S); also elsewhere on the board
GND: Q2.2 (E); also elsewhere on the board
LCD_EN: Q2.1 (B); also elsewhere on the board
LCD_PWR: Q1.3 (D); also elsewhere on the board
unnamed: Q1.1 (G), Q2.3 (C)
